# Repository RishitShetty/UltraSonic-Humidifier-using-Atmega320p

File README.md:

Ultrasonic Humidifier Controlled by ATmega328P and HC-05 Bluetooth 

The ultrasonic humidifier project idea was to test the effectiveness of the prototype using a 8 Bit 
microcontroller Atmega328P with the Bluetooth module and other peripherals. This project was 
done to evaluate the author’s (Me) capabilities in compact PCB designing and coding 
capabilities in embedded C programming.  
Project Motivation: The basic use of an ultrasonic humidifier is to convert the liquid 
into mist particles useful for a spray-based mechanism in small devices mainly for the 
purpose of cleaning and getting into hard-to-get access places. Integrating it with a 
Bluetooth module makes the system more robust and easier to use and integrate with 
other modules with the add of no cost at all. 
Objectives: 
o Provide ON/OFF control of an ultrasonic transducer via push button or 
smartphone. 
o Maintain safe, efficient power management. 
o Keep BOM and PCB footprint minimized (cost & size). 
o Ensure reliable wireless communication (HC-05). 
2. Design Explanation 
2.1 System Overview & Block Diagram 
 High-Level Blocks: 
1. Power Supply (12 V Battery or Adapter → AMS1117 → 5 V Rail) 
2. ATmega328P Microcontroller 
3. HC-05 Bluetooth Module 
4. Manual Push Button Input 
5. MOSFET + Flyback Diode → Ultrasonic Transducer 
6. Status LED Indicator 
2.2 Component Selection Rationale 
1. ATmega328P Microcontroller 
o The Atmega328P is a high performance yet low power consumption 8-bit micro
controller with clock execution of 131 powerful execution. It serves as a perfect 
micro-controller for this system as we don’t require a MCU more powerful than 
this and power consumption is low enough. It is a simple RISC instruction set 
with 32KB of flash memory making it optimal. 
2. HC-05 Bluetooth Module 
o The HC-05 Bluetooth module is a common and cheap 2.4 GHz BL module which 
can be used easily integrated with the Atmega328P as it uses UART protocol for 
interfacing. 
3. MOSFET (IRFZ44N) 
o The MOSFET used in the circuit design was IRFZ44N because of its moderately 
compact footprint size and cost and effectiveness. It can handle up to 55V of drain 
source voltage and drain gate voltage and around 40 amps of drain current. 
4. Ultrasonic Transducer (e.g., 20 mm, 1.7 MHz Module) 
o In the KiCAD design the ultrasonic transducer used was a general one with a 
small footprint so as to accommodate it in the overall design. As we are using 12V 
input voltage for the ultrasonic transducer we need the switching mechanism 
using the MOSFET. The Atmega320P GPIO pins can only handle 5V and current 
in the milliamperes which is not sufficient for the sensor. 
5. AMS1117-5.0 Voltage Regulator 
o The AMS1117 is a common voltage regulator used in multiple breakout boards for 
regulating either 3.3 or 5 V depending upon the use. It’s cheap and effectiveness 
made it optimal in this project. 
6. Push Button & Debounce 
o The push button included was a pull-up which means it is always high until 
pressed making it low, debouncing was needed in order to make the small 
oscillations redundant and not to be considered as a press. 
7. Status LED 
o To give us an indication of the state of the system as we have two mechanisms to 
switch it, which is the button and the Bluetooth function which may make it 
confusing to figure out the status. 
8. Passive Components (Resistors, Capacitors, Flyback Diode) 
o The reset button is designed as a pull-up with a 10K ohm resistor, a 220 ohm 
resistor added to the gate so as to not let excess current into the gate of the 
MOSFET, Flyback diode to not allow reverse current flow to the MOSFET which 
could potentially damage it, and voltage dividers are used to reduce 5 volts to 3.3 
volts into the Rx and Tx pins of the Bluetooth module.  

2.3 Control Logic Flow 
1. Power-On Initialization 
o Initialize GPIO: Push button (input with pull-up), MOSFET pin (output LOW), 
LED pin (output LOW). 
o Initialize UART (UBRR=103 for 9600 bps @16 MHz). 
o Set mode = MANUAL by default. 
2. Main Loop 
while (true): 
    if (mode == MANUAL): 
        if (button_pressed()): 
            toggle_humidifier() 
            blink_LED()  // optional feedback 
            delay_ms(200)  // debounce 
    if (UART data available): 
        cmd = uart_receive() 
        if (cmd == '1'): 
            humidifier_on() 
            mode = BLUETOOTH 
        else if (cmd == '0'): 
            humidifier_off() 
            mode = BLUETOOTH 
        else if (cmd == 'M'): 
            mode = MANUAL 
 
The Bluetooth mode switching and manual mode switching are completely independent of each 
other and can work simultaneously, as you can see there are separate loops for each function. 
 
2.4 PCB & Hardware Considerations 
 HC-05 Placement & Antenna Keep-Out 
o The Bluetooth modules antenna was left on a void ground plane to improve range 
and also distanced from the MOSFET so to reduce EMI which could cause noise 
and subsequently loss of data. 
 MOSFET & Power Traces 
o The MOSFET’s position was thoroughly thought about as it could produce EMI 
and disrupt signal and caries high voltage. The traces used for the power lanes 
were thicker compared to the rest, 0.254 mm trace for the power line and 0.177 
mm for the rest. 
 Decoupling Capacitors 
o The decoupling capacitors are supposed to be as close to AMS1117 as possible so 
as to minimize power loss. 
 Reset Button & Pull-Up 
o Similarly, the button and the 10 Kohm pull-up has to be close to the push button 
to account for resistance. 
 Battery Pad Footprint 
o Battery pads are a must as our circuit needs 12V external supply to operate. 
 
3. Challenges & Solutions 
Here we will discuss the issues faced in circuit designing and how I worked over it. 
3.1 Signal Interference (Bluetooth & Switching Noise) 
Since EMI is always an issue circuit designers face, it will cause constructive and destructive 
interference with the low current data lines and result in data loss. So, I decided to keep the Rx 
and Tx lines distanced from the high voltage lines and the MOSFET which could also be a 
reason for EMI due to switching. 
3.2 Mode Switching Logic (Manual vs. Bluetooth) 
There are possibilities when the button switching could collide with the Bluetooth function and 
cause a race condition. Hence, a priority logic would definitely prove to rectify this issue and 
also debouncing the push button handles it well enough. 
3.3 Moisture & Environmental Concerns 
Depending upon how the ultrasonic humidifier module would be used, the cause of corrosion 
could be a concern. This is the reason I incorporated a small footprint for the ultrasonic 
transducer which serves as pads and can be used separately from the PCB. 
4. Block Diagram 
Instructions: Create a simple block diagram (e.g., in Microsoft PowerPoint, draw.io, or hand
sketch and import) showing these interactions: 
1. 12 V Battery / Adapter → AMS1117 → 5 V Rail 
2. 12 V Battery → Ultrasonic Transducer → 12 V Rail 
3. 5 V Rail → ATmega328P, HC-05, Status LED 
4. ATmega328P ↔ HC-05 (UART TX/RX) 
5. ATmega328P → MOSFET Gate  
6. MOSFET Drain → Ultrasonic Transducer 
7. Push Button → ATmega328P (GPIO) 
8. Status LED ← ATmega328P (GPIO) 
5. Potential Production Optimizations 
[Discuss how the design could be optimized for a production run. Cover cost reduction, board 
size shrinkage, alternative components, and manufacturing considerations.] 
1. Component Consolidation 
o For future considerations a better MCU with high clock frequency and if more 
functions were required for a production and market scenario. 
2. PCB Layout Miniaturization 
o Resistors, capacitors and other components footprint size could be reduced from 
current 0805 to per se 0402 for example and MCU size also can be reduced 
considerably if changed.

4. Assembly & Testing Jigs 
o More debugging lines in code would certainly help gather information of certain 
failures and help with failure and fault handling. Along with more testing and the 
addition of functions in future, more testing points need to be added.
 6. Conclusion 
Working on this led me to gain more in-depth knowledge on the Atmega328P and although it was 
an evaluatory task for me, this task did not really push me to any limits but helped me learn a 
couple of relevant things. 
7. References 
1. ATmega328P Datasheet, Microchip Technology. 
2. HC-05 Bluetooth Module Datasheet. 
3. AMS1117-5.0 Datasheet, Advanced Monolithic Systems. 
4. IRFZ44N MOSFET Datasheet, International Rectifier. 
5. https://chatgpt.com, for some assistance in embedded C.

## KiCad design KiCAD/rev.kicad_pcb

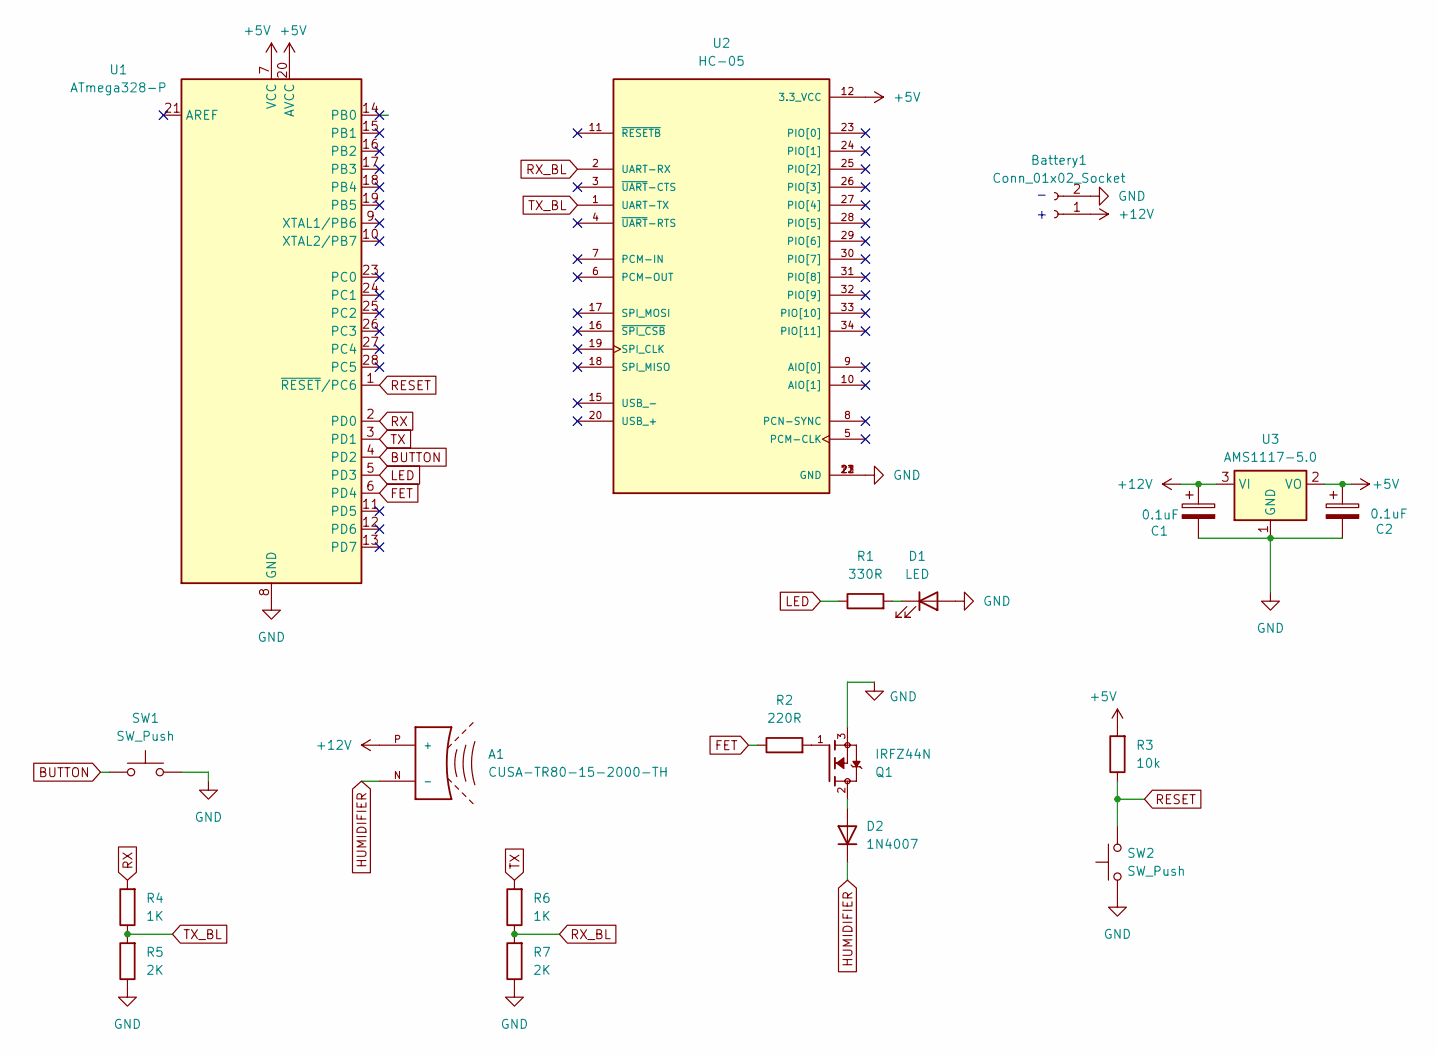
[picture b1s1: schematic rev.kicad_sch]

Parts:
A1: CUSA-TR80-15-2000-TH; XDCR_CUSA-TR80-15-2000-TH; PARTREV 1.0
Battery1: Conn_01x02_Socket; PinSocket_1x02_P2.54mm_Horizontal
C1, C2: 0.1uF; CP_EIA-1608-08_AVX-J
D1: LED; LED_1210_3225Metric_Pad1.42x2.65mm_HandSolder
D2: 1N4007; D_DO-41_SOD81_P2.54mm_Vertical_AnodeUp
Q1: IRFZ44N; TO254P1016X419X2286-3; PARTREV 09/21/10
R1: 330R; R_0805_2012Metric_Pad1.20x1.40mm_HandSolder
R2: 220R; R_0805_2012Metric_Pad1.20x1.40mm_HandSolder
R3: 10k; R_0805_2012Metric_Pad1.20x1.40mm_HandSolder
R4, R6: 1K; R_0805_2012Metric_Pad1.20x1.40mm_HandSolder
R5, R7: 2K; R_0805_2012Metric_Pad1.20x1.40mm_HandSolder
SW1, SW2: SW_Push; SW_Push_1P1T_XKB_TS-1187A
U1: ATmega328-P; DIP-28_W7.62mm
U2: HC-05; XCVR_HC-05; PARTREV v1.0
U3: AMS1117-5.0; SOT-223-3_TabPin2

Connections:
+5V: C2.1, R3.2, U1.7 (VCC), U1.20 (AVCC), U2.12 (3.3_VCC), U3.2 (VO)
+12V: A1.P (+), Battery1.1, C1.1, U3.3 (VI)
BUTTON: SW1.1, U1.4 (PD2)
FET: R2.1, U1.6 (PD4)
GND: Battery1.2, C1.2, C2.2, D1.2 (A), Q1.3, R5.1, R7.1, SW1.2, SW2.1, U1.8 (GND), U1.22 (GND), U2.13 (GND), U2.21 (GND), U2.22 (GND), U3.1 (GND)
HUMIDIFIER: A1.N (-), D2.1 (K)
LED: R1.1, U1.5 (PD3)
unnamed: D1.1 (K), R1.2
unnamed: D2.2 (A), Q1.2
unnamed: Q1.1, R2.2
RESET: R3.1, SW2.2, U1.1 (~RESET/PC6)
RX: R4.2, U1.2 (PD0)
RX_BL: R6.1, R7.2, U2.2 (UART-RX)
TX: R6.2, U1.3 (PD1)
TX_BL: R4.1, R5.2, U2.1 (UART-TX)

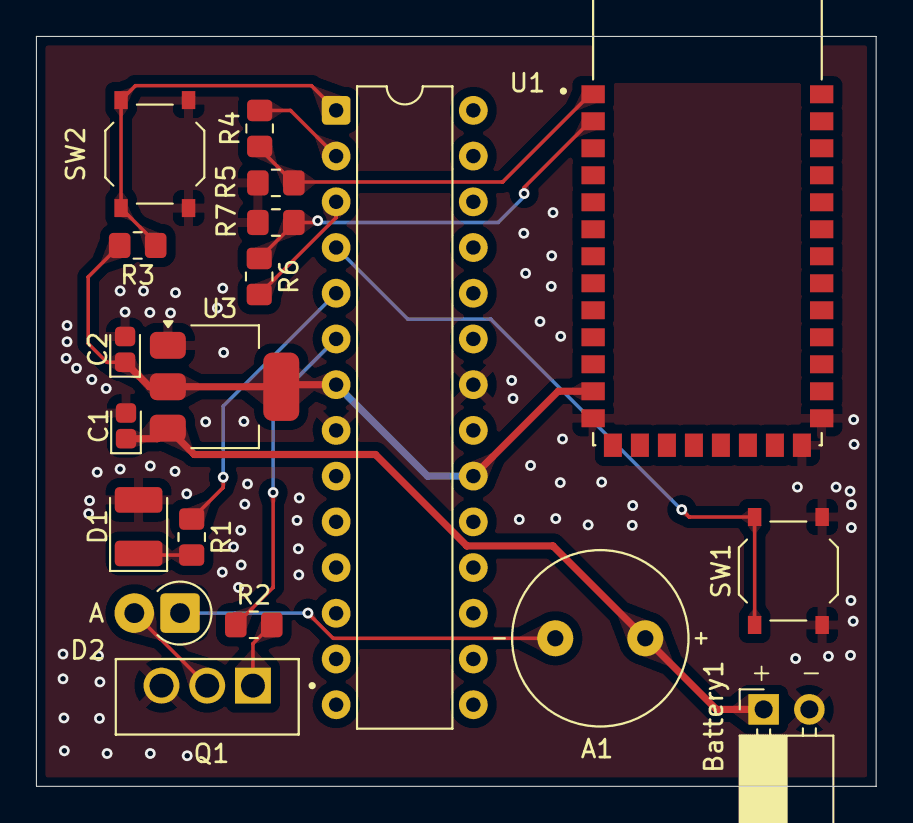
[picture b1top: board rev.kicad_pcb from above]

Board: 2 copper layers, 46.6 x 41.7 mm, 19 parts (0 on the bottom side), 15 nets.

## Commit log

2025-08-13 Added all the files together
2025-08-13 Added the KiCAD folder
2025-09-10 Update README.md
    Image added
